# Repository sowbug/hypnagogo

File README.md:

The Hypna Go Go: Hypnagogic Goggles
===================================

This is adapted from an [Instructables
project](http://www.instructables.com/id/The-Lucid-hypnagogo/). With a
simple ATtiny13-based circuit, this project helps nudge your dreaming brain
into an *Inception*-like state of awareness. At least, that's the theory. So
far, I have slept through the whole experience and remembered nothing.

See [the project](https://github.com/sowbug/hypnagogo) on GitHub, and have a look at an untested [Mouser cart](http://www.mouser.com/ProjectManager/ProjectDetail.aspx?AccessID=e0a3dbcca8).

Features
========

* Tuned for a typical 8- or 9-hour nighttime sleep, with long separations between inductions early in the night, and rapid inductions near morning.
* Nap mode, with quick inductions in an 80-minute program.
* Auto-shutoff at program end.
* Manual shutoff by holding down button for two seconds.
* Extremely low power consumption. A 40mAh CR1220 should last months or years.

Operation
=========

When the battery is first installed, the device is in the power-off state. Tap the button to turn it on. You'll see steady lights for about two seconds. The 9-hour sleep cycle has begun. Place the board over your eyes. I use a sleep mask to hold mine in place.

The sleep cycle starts with an idle state of about 3.5 hours. When idle ends, dream induction begins. During induction, the LEDs alternate gently blinking for about 30 seconds. The device then returns to idle, but the idle period each time is halved: 1.75 hours, then 52 minutes, then 26, and so on down to a minimum of 8 minutes separating each induction. After 16 consecutive eight-minute inductions, the device powers off.

For example:

1. Go to sleep at 10:30pm. Turn on the device.
2. The first induction will happen around 2am.
3. The second induction will happen one hour and 45 minutes later, at 3:45am.
4. At 5:16am, the device will begin inductions every 8 minutes.
5. At about 7:30am, the device shuts off.

This pattern corresponds to a typical human's REM-sleep schedule (short and sparse at the beginning of sleep, long and frequent toward morning).

Nap mode starts with a button tap while the device is idling (i.e., powered on but not blinking). The only difference is that it starts with an immediate induction followed by a 16-minute idle time, and it powers off after only eight consecutive 8-minute inductions, for a total cycle of about 80 minutes.

Hold the button down for two seconds to turn the device off. You'll see a quick blink sequence to confirm shutdown.

To Do
=====

* Run the 'tiny at an even slower speed. 128KHz ought to be fine, and it'll use even less power.
* Experiment with different light patterns.

Disclaimer
==========

As stated above, this project hasn't yet done anything for me. And if for any
reason you have problems wearing a circuit board on your head at night or
lights flashing in your eyes, you should probably avoid this project.

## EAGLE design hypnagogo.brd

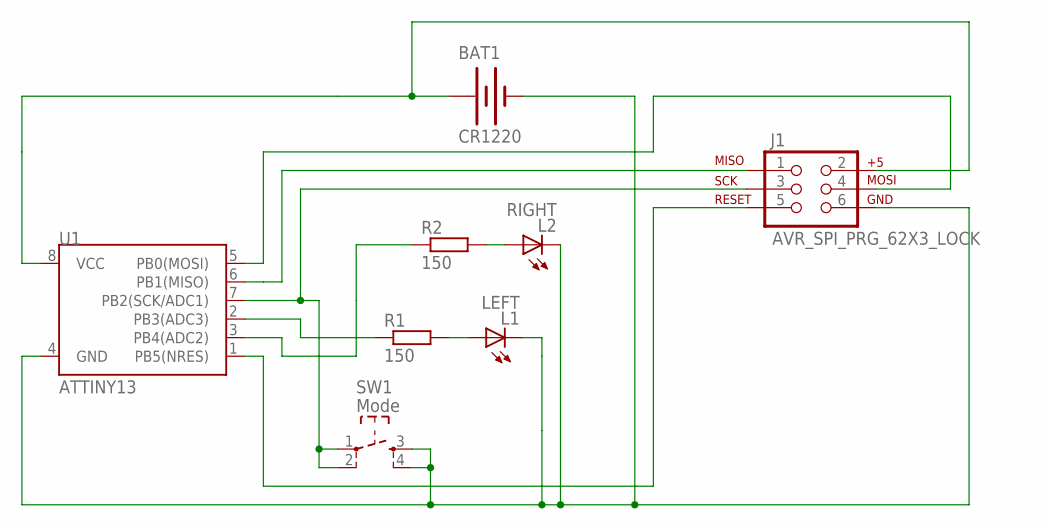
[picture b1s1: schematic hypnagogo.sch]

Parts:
BAT1: CR1220; BATTCON_12MM
J1: AVR_SPI_PRG_62X3_LOCK; 2X3_LOCK
L1: LEFT; LED-3MM
L2: RIGHT; LED-3MM
R1, R2: 150; R805
SW1: Mode; SW_TACT_SMALL
U1: ATTINY13; SO08

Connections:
/RESET: J1.5, U1.1 (PB5(NRES))
GND: BAT1.GND (-), J1.6, L1.K (C), L2.K (C), SW1.3, SW1.4, U1.4 (GND)
L1-R: L1.A, R1.2
L2: R2.1, U1.3 (PB4(ADC2))
L2-R: L2.A, R2.2
MISO: J1.1, U1.6 (PB1(MISO))
MOSI: J1.4, U1.5 (PB0(MOSI))
PB2/SCK: J1.3, SW1.1, SW1.2, U1.7 (PB2(SCK/ADC1))
PB3: R1.1, U1.2 (PB3(ADC3))
VCC: BAT1.PWR@1 (+), J1.2, U1.8 (VCC)

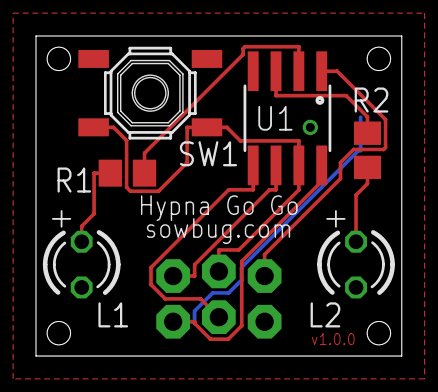
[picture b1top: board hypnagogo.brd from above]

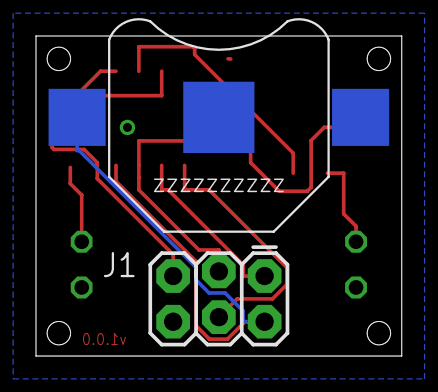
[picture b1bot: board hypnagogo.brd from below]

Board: 2 copper layers, 20.3 x 17.8 mm, 8 parts (2 on the bottom side), 10 nets.

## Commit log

2012-04-08 New.
2012-04-08 Formatting.
2012-04-08 Avoid linking in floating-point library.
2012-04-08 Optimize for 8 hours of sleep.
2012-04-08 Typos, clarity.
2012-04-09 Simplify button code.
2012-04-09 Avoid possible case where interrupts overflow.
2012-04-10 Code cleanup. Fix static initialization.
2012-04-10 EAGLE schematic.
2012-04-10 Place markers for LED anode.
2012-04-10 Images.
2012-04-10 Renamed.
2012-04-10 Updated.
2012-04-10 Code cleanliness.
2012-04-11 Added power jumper. Fixed orientation of battery holder.
2012-04-11 Updated images.
2012-04-12 Don't need the power switch. Single button acts as both.
2012-04-13 Moved hardware files to https://github.com/sowbug/dream-machine-hw.
2012-04-13 Auto-shutoff. Nap mode.
2012-04-14 Fixed incompatibility between pin layout and ISP.
2012-04-14 Faster dream-induction flashing. More time between nap inductions. Debounce.
2012-04-14 Refactor in preparation for slowing down system clock.
2012-04-14 Simplify button code. Add 'make prod' target.
2012-04-14 Program fuses.
2012-04-14 Made PWM CPU-speed independent.
2012-04-14 Parameterize old hardware version.
2012-04-15 Refactor, improve instructions, recalibrate nap/sleep cycles.
2012-04-15 Added sample sleep schedule.
2012-04-15 Made feature list a bit less specific so I don't have to keep fixing it.
2012-04-15 Rename to hypnagogo.
2012-05-03 Read AVR4027. Loops count down.
2012-05-03 Not so bright.
2012-05-09 Reunited hypnagogo-hw with the firmware.
2012-05-09 Don't require sudo to program.
2012-05-09 Update links.
2012-05-09 Take advantage of static initializers.
2012-05-09 Add datasheets.
2012-05-10 Fade in more gently to avoid shocking subject into consciousness.
2012-05-10 More specific type.

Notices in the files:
parts and their libraries:
SparkFun: Licensing: CC v3.0 Share-Alike You are welcome to use this library for commercial purposes.
